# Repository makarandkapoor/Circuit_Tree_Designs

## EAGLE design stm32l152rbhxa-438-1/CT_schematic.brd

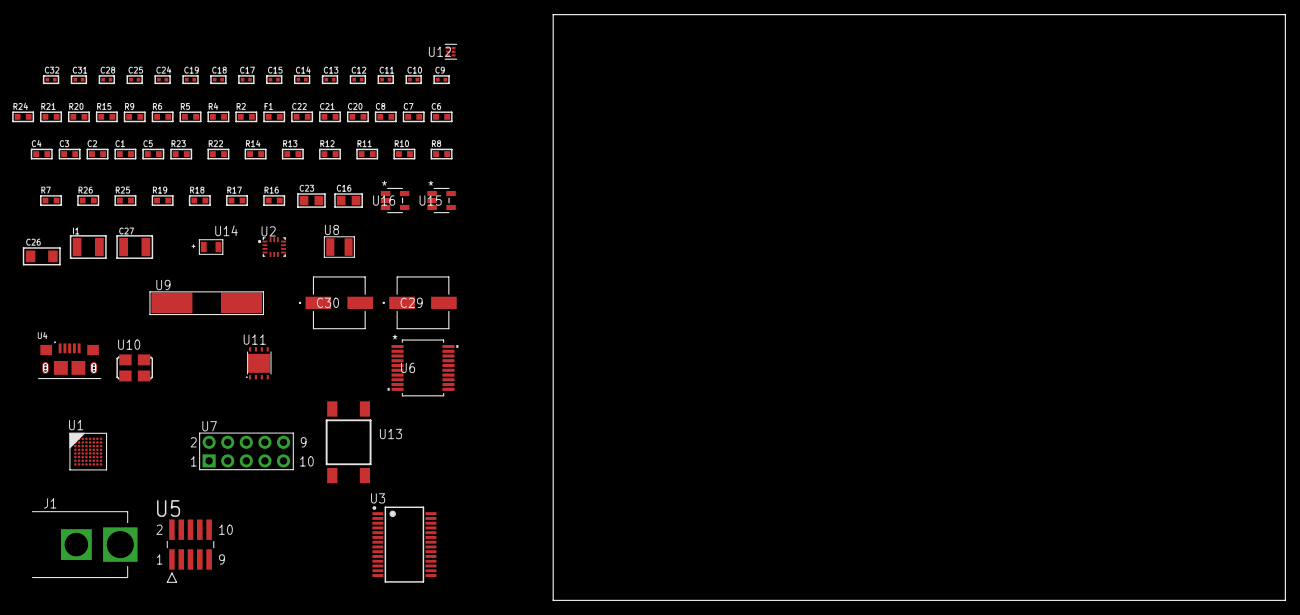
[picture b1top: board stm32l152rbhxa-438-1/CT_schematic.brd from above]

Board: 2 copper layers, 169.6 x 80.0 mm, 75 parts (0 on the bottom side), 55 nets, no tracks yet.

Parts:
C1, C2, C3, C4, C6: 1e-07; C0603
C5: 4.7e-06; C0603
C7: 1e-08; C0603
C8, C20, C21, C22: 1e-06; C0603
C9, C10, C11, C12: 1e-11; C0402
C13, C14, C15, C17, C18, C19, C28: 1e-07; C0402
C16, C23: 4.7e-06; C0805
C24, C25, C31, C32: 1e-08; C0402
C26: 1e-05; C1206
C27: 1e-05; C1210
C29, C30: 0.0001; EXV-9H
F1: 240.0; L0603
I1: 1.5e-05; L1210
J1: PJ-037B; PJ-037B_PACKAGE
R2, R21: 1000.0; R0603
R4, R9: 4700.0; R0603
R5, R6: 2200.0; R0603
R7, R8, R10, R11, R12, R13, R14, R22, R23: 10000.0; R0603
R15: 5.0; R0603
R16, R17, R18, R19: 100000.0; R0603
R20: 2231.0; R0603
R24: 9100.0; R0603
R25: 680000.0; R0603
R26: 120000.0; R0603
U1: STM32L152RBH6A; TFBGA64
U2: BMG250; LGA-14
U3: FT232RL-REEL; SSOP-28
U4: 10118193-0001LF; FCI_10118193-0001LF
U5: FTSH-105-01-L-DV-K; SAMTEC_FTSH-105-01-L-DV-K
U6: MAX3218EAP+T; SSOP-20
U7: HTSS-105-01-G-D
U8: ABS07-32.768KHZ-7-T
U9: ABLS-25.000MHZ-B2F-T
U10: ASFL1-12MHZ-NCS; ASFL1
U11: LP3878SDX-ADJ/NOPB; WSON-8
U12: TPS3895ADRYR; SON-6
U13: 4-1437565-2; SW_4-1437565-2
U14: Q65110A2395; LGM67K-G1J2-24-Z
U15, U16: nc7sz125m5x; NC7SZ125M5X

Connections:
CLK_CRYSTAL_U1_A1: C9.1, U1.A1, U8.1
CLK_CRYSTAL_U1_B1: C10.1, U1.B1, U8.2
CLK_CRYSTAL_U1_C1: C11.1, U1.C1, U9.1
CLK_CRYSTAL_U1_D1: C12.1, U1.D1, U9.2
CLK_U3_27: U3.27, U10.3
GND: C1.2, C2.2, C3.2, C4.2, C5.2, C6.2, C7.2, C8.2, C9.2, C10.2, C11.2, C12.2, C13.2, C14.2, C15.2, C16.2, C17.2, C18.2, C19.2, C20.2, C21.2, C22.2, C24.2, C25.2, C26.2, C27.2, C28.2, C29.2, C30.2, C31.2, C32.2, J1.2, R2.2, R7.2, R11.2, R15.2, R21.2, R24.2, R26.2, U1.C2, U1.D4, U1.D5, U1.D6, U1.F1, U2.1, U2.6, U2.7, U3.7, U3.18, U3.21, U3.25, U3.26, U4.5, U4.6, U4.7, U4.8, U4.9, U5.3, U5.5, U6.5, U6.17, U6.20, U7.9, U10.2, U11.3, U11.PAD, U12.2, U14.C, U15.2, U15.3, U16.1, U16.3
NET_U1_A3: R6.1, U1.A3, U2.14
NET_U1_B2: C6.1, U1.B2
NET_U1_B3: R5.1, U1.B3, U2.13
NET_U1_B4: R7.1, U1.B4
NET_U1_E1: R4.1, U1.E1, U16.4
NET_U1_H1: C7.1, C8.1, F1.1, U1.G1, U1.H1
NET_U1_H8: U13.3, U13.4
NET_U2_12: R8.1, U2.12
NET_U3_14: R10.1, U3.14
NET_U3_17: C17.1, U3.17
NET_U3_19: R11.1, U3.19
NET_U4_1: R9.1, U4.1
NET_U4_2: U3.16, U4.2
NET_U4_3: U3.15, U4.3
NET_U5_9: R15.1, U5.9
NET_U6_1: I1.1, U6.1
NET_U6_2: R16.1, U6.2
NET_U6_3: R17.1, U6.3
NET_U6_4: R18.1, U6.4
NET_U6_15: C22.1, U6.15
NET_U6_16: C23.2, U6.16
NET_U6_18: C23.1, U6.18
NET_U6_19: C21.1, U6.19
NET_U7_3: U6.12, U7.3
NET_U7_4: U6.11, U7.4
NET_U7_5: U6.14, U7.5
NET_U7_6: U6.13, U7.6
NET_U11_1: C25.1, U11.1
NET_U11_6: R20.2, R21.1, U11.6
NET_U11_8: R19.1, U11.8
NET_U12_1: R23.1, R24.1, U12.1
NET_U12_3: R25.2, R26.1, U12.3
NET_U12_4: R22.1, U12.4, U15.4, U16.2
NET_U13_1: R2.1, U13.1, U13.2
PROC_GPIO_TO_U2_INT1: U1.A2, U2.4
PROC_SYS_JTCK_SWCLK: R13.1, U1.A7, U5.4
PROC_SYS_JTDO_TRACESWO: U1.A5, U5.6
PROC_SYS_JTMS_SWDIO: R14.1, U1.A8, U5.2
PROC_USART1_CTS: U1.C8, U3.3
PROC_USART1_RTS: U1.B8, U3.11
PROC_USART1_RX: U1.C3, U3.1
PROC_USART1_TX: U1.C7, U3.5
PROC_USART2_CTS: U1.G2, U6.8
PROC_USART2_RTS: U1.H2, U6.10
PROC_USART2_RX: U1.G3, U6.9
PROC_USART2_TX: U1.F3, U6.7
RST_OUT_U5_JTAG_RST_B: R12.1, U5.10, U15.1
VCC_S1_9V3: C26.1, C29.1, C30.1, J1.1, R19.2, U11.4
VCC_TIER1_3V3: C1.1, C2.1, C3.1, C4.1, C5.1, C13.1, C14.1, C15.1, C16.1, C18.1, C19.1, C20.1, C24.1, C27.1, C28.1, C31.1, C32.1, F1.2, I1.2, R4.2, R5.2, R6.2, R8.2, R10.2, R12.2, R13.2, R14.2, R16.2, R17.2, R18.2, R20.1, R22.2, R23.2, R25.1, U1.D2, U1.E4, U1.E5, U1.E6, U2.5, U2.8, U3.4, U3.20, U5.1, U6.6, U10.4, U11.5, U12.6, U15.5, U16.5

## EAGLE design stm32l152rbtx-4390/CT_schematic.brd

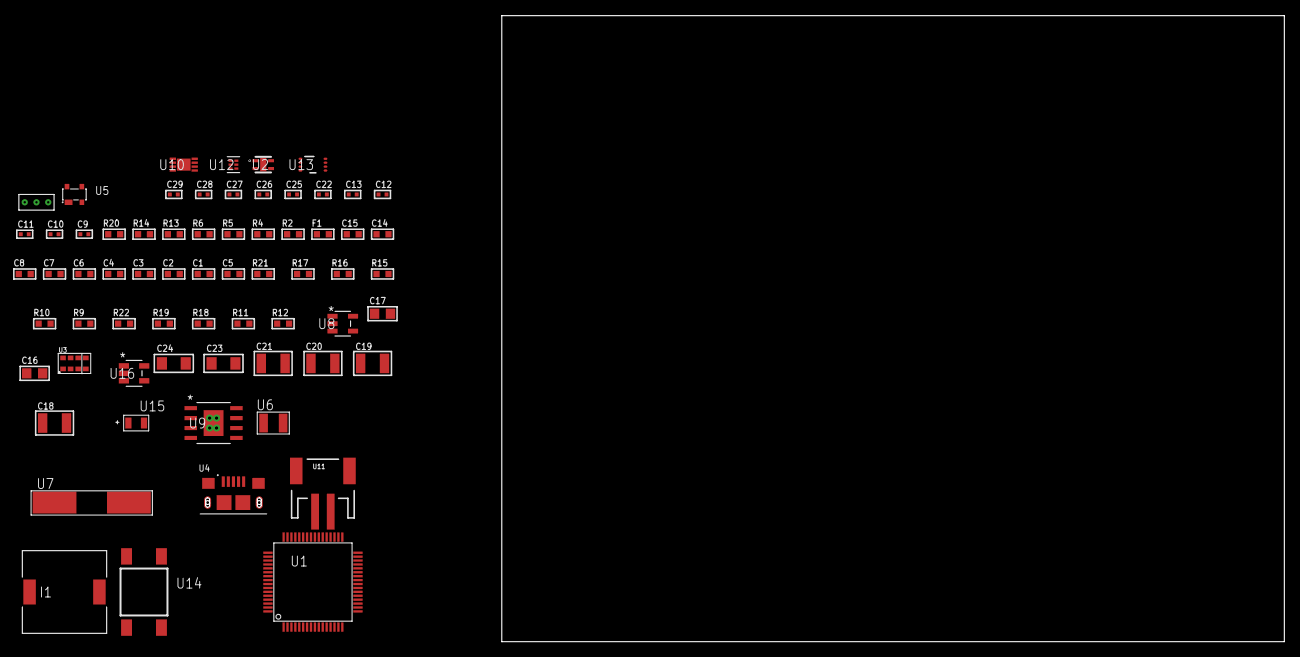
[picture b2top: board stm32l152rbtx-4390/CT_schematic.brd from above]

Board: 2 copper layers, 66 parts (0 on the bottom side), 34 nets, no tracks yet.

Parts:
C1, C2, C3, C4, C6: 1e-07; C0603
C5: 4.7e-06; C0603
C7: 1e-08; C0603
C8, C14, C15: 1e-06; C0603
C9, C10, C11, C12: 1e-11; C0402
C13, C22, C26, C28: 1e-07; C0402
C16, C17: 1e-05; C0805
C18, C19, C20, C21: 1e-05; C1210
C23, C24: 1e-05; C1206
C25, C27, C29: 1e-08; C0402
F1: 240.0; L0603
I1: 5.2e-06; DR1040
R2: 1000.0; R0603
R4: 4700.0; R0603
R5, R6, R14: 2200.0; R0603
R9, R10, R15, R16, R21: 10000.0; R0603
R11: 490000.0; R0603
R12: 1000000.0; R0603
R13: 3600.0; R0603
R17: 82000.0; R0603
R18: 300000.0; R0603
R19: 120000.0; R0603
R20: 2000.0; R0603
R22: 200000.0; R0603
U1: STM32L152RBT6; LQFP64
U2: Si7034-A10-IM; SI7034-A10-IM
U3: TMD27711; SMD-8
U4: 10118193-0001LF; FCI_10118193-0001LF
U5: prtr5v0u2ax; SOT143B
U6: ABS07-32.768KHZ-7-T
U7: ABLS-25.000MHZ-B2F-T
U8: ltc3406es5; TSOT-23-5
U9: MIC5234YME; SOIC-8_EP
U10: MCP73831T-2ACI/MC; DFN8_2X3MC
U11: S2B-PH-SM4-TB(LF)(SN); JST-2-SMD
U12: TPS3895ADRYR; SON-6
U13: LSF0102DCTR; DCU0008A_N
U14: 4-1437565-2; SW_4-1437565-2
U15: Q65110A2395; LGM67K-G1J2-24-Z
U16: nc7sz125m5x; NC7SZ125M5X
U17: Dummy; DUMMY_PACKAGE_139

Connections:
CLK_CRYSTAL_U1_3: C9.1, U1.3, U6.1
CLK_CRYSTAL_U1_4: C10.1, U1.4, U6.2
CLK_CRYSTAL_U1_5: C11.1, U1.5, U7.1
CLK_CRYSTAL_U1_6: C12.1, U1.6, U7.2
GND: C1.2, C2.2, C3.2, C4.2, C5.2, C6.2, C7.2, C8.2, C9.2, C10.2, C11.2, C12.2, C13.2, C14.2, C15.2, C16.2, C17.1, C17.2, C18.2, C19.2, C20.2, C21.2, C22.2, C23.2, C24.2, C25.2, C26.2, C27.2, C28.2, C29.2, R2.2, R9.2, R11.2, R14.2, R17.2, R19.2, R20.2, U1.12, U1.18, U1.31, U1.47, U1.63, U2.5, U3.3, U4.5, U4.6, U4.7, U4.8, U4.9, U5.1, U8.2, U9.7, U9.EPAD, U10.6, U10.9, U11.2, U12.2, U13.1, U15.C, U16.1, U16.3, U17.1
INPUT_USBPOWER_5V: C23.1, R21.2, U4.1, U5.4, U10.1, U10.2
NET_U1_1: C6.1, U1.1
NET_U1_7: R4.1, U1.7, U16.4
NET_U1_13: C7.1, C8.1, F1.1, U1.13
NET_U1_58: R5.1, U1.58, U2.2
NET_U1_59: R6.1, U1.59, U2.4
NET_U1_60: R9.1, U1.60
NET_U1_62: U14.3, U14.4
NET_U3_7: R10.1, U3.7
NET_U8_3: I1.1, U8.3
NET_U8_5: R11.1, R12.1, U8.5
NET_U8_ATNET_3: I1.2, R12.2
NET_U9_4: R13.2, R14.1, U9.4
NET_U10_5: R21.1, U10.5
NET_U10_8: R20.1, U10.8
NET_U12_1: R16.1, R17.1, U12.1
NET_U12_3: R18.2, R19.1, U12.3
NET_U12_4: R15.1, U12.4, U16.2
NET_U13_8: R22.1, U13.8
NET_U14_1: R2.1, U14.1, U14.2
PROC_I2C2_SCL_TOXCVR: U3.2, U13.5
PROC_I2C2_SDA_TOXCVR: U3.8, U13.6
PROC_PC0: U1.8, U17.3
PROC_PC13_WKUP2: U1.2, U17.2
PROC_USB_DM: U1.44, U4.2, U5.3
PROC_USB_DP: U1.45, U4.3, U5.2
VCC_S1_3V7: C16.1, C18.1, C19.1, C24.1, U8.4, U9.5, U9.8, U10.3, U10.4, U11.1
VCC_TIER1_1V8: C1.1, C2.1, C3.1, C4.1, C5.1, C13.1, C17.2, C22.1, C27.1, C28.1, C29.1, F1.2, I1.2, R4.2, R5.2, R6.2, R12.2, R15.2, R16.2, R18.1, U1.19, U1.32, U1.48, U1.64, U2.1, U12.6, U13.2, U16.5
VCC_TIER1_3V0: C14.1, C15.1, C20.1, C21.1, C25.1, C26.1, R10.2, R13.1, R22.2, U3.1, U3.4, U9.1, U13.7

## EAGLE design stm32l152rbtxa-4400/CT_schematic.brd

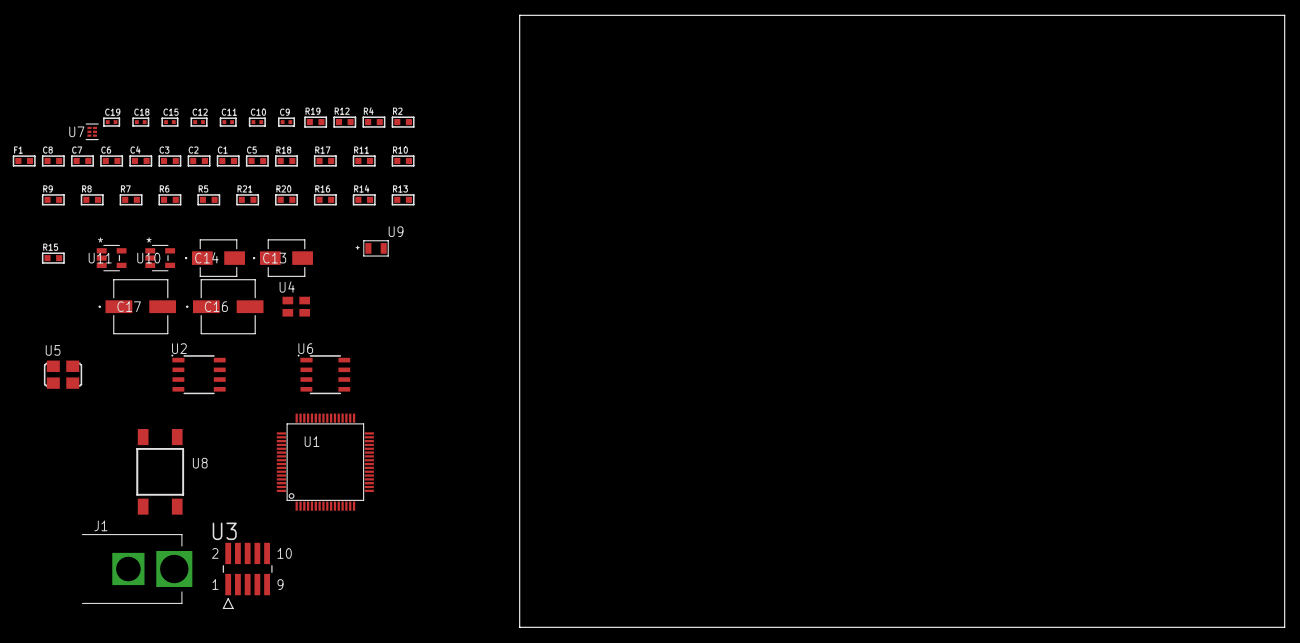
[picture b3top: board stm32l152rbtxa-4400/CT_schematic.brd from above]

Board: 2 copper layers, 100.0 x 80.0 mm, 51 parts (0 on the bottom side), 28 nets, no tracks yet.

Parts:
C1, C2, C3, C4, C6: 1e-07; C0603
C5: 4.7e-06; C0603
C7: 1e-08; C0603
C8: 1e-06; C0603
C9, C11, C12, C18, C19: 1e-08; C0402
C10, C15: 1e-07; C0402
C13: 1e-06; EXV-9B
C14: 2.2e-06; EXV-9B
C16, C17: 0.0001; EXV-9H
F1: 240.0; L0603
J1: PJ-037B; PJ-037B_PACKAGE
R2: 1000.0; R0603
R4: 4700.0; R0603
R5, R6, R7, R8, R9, R10, R11, R17, R18: 10000.0; R0603
R12: 5.0; R0603
R13, R14, R16: 100000.0; R0603
R15: 164658.62; R0603
R19: 9100.0; R0603
R20: 680000.0; R0603
R21: 120000.0; R0603
U1: STM32L152RBT6A; LQFP64
U2: AT25640B-SSHL-T; SOIC-8
U3: FTSH-105-01-L-DV-K; SAMTEC_FTSH-105-01-L-DV-K
U4: ASEK-32.768KHz-ECST; ASEK
U5: ASFL1-25MHZ-NCS; ASFL1
U6: LP2954AIMX/NOPB; LP2954
U7: TPS3895ADRYR; SON-6
U8: 4-1437565-2; SW_4-1437565-2
U9: Q65110A2395; LGM67K-G1J2-24-Z
U10, U11: nc7sz125m5x; NC7SZ125M5X

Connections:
CLK_U1_3: U1.3, U4.3
CLK_U1_5: U1.5, U5.3
GND: C1.2, C2.2, C3.2, C4.2, C5.2, C6.2, C7.2, C8.2, C9.2, C10.2, C11.2, C12.2, C13.2, C14.2, C15.2, C16.2, C17.2, C18.2, C19.2, J1.2, R2.2, R5.2, R12.2, R16.2, R19.2, R21.2, U1.12, U1.18, U1.31, U1.47, U1.63, U2.4, U3.3, U3.5, U4.2, U5.2, U6.4, U7.2, U9.C, U10.2, U10.3, U11.1, U11.3
NET_U1_1: C6.1, U1.1
NET_U1_7: R4.1, U1.7, U11.4
NET_U1_13: C7.1, C8.1, F1.1, U1.13
NET_U1_60: R5.1, U1.60
NET_U1_62: U8.3, U8.4
NET_U2_3: R6.1, U2.3
NET_U2_7: R8.1, U2.7
NET_U3_9: R12.1, U3.9
NET_U6_3: R14.1, U6.3
NET_U6_5: R13.1, U6.5
NET_U6_7: R15.2, R16.1, U6.7
NET_U7_1: R18.1, R19.1, U7.1
NET_U7_3: R20.2, R21.1, U7.3
NET_U7_4: R17.1, U7.4, U10.4, U11.2
NET_U8_1: R2.1, U8.1, U8.2
PROC_SPI1_MISO: U1.22, U2.2
PROC_SPI1_MOSI: U1.23, U2.5
PROC_SPI1_NSS: R7.1, U1.20, U2.1
PROC_SPI1_SCK: U1.21, U2.6
PROC_SYS_JTCK_SWCLK: R10.1, U1.49, U3.4
PROC_SYS_JTDO_TRACESWO: U1.55, U3.6
PROC_SYS_JTMS_SWDIO: R11.1, U1.46, U3.2
RST_OUT_U3_JTAG_RST_B: R9.1, U3.10, U10.1
VCC_S1_12V1: C13.1, C16.1, C17.1, J1.1, R14.2, U6.8
VCC_TIER1_3V3: C1.1, C2.1, C3.1, C4.1, C5.1, C9.1, C10.1, C11.1, C12.1, C14.1, C15.1, C18.1, C19.1, F1.2, R4.2, R6.2, R7.2, R8.2, R9.2, R10.2, R11.2, R13.2, R15.1, R17.2, R18.2, R20.1, U1.19, U1.32, U1.48, U1.64, U2.8, U3.1, U4.4, U5.4, U6.1, U7.6, U10.5, U11.5

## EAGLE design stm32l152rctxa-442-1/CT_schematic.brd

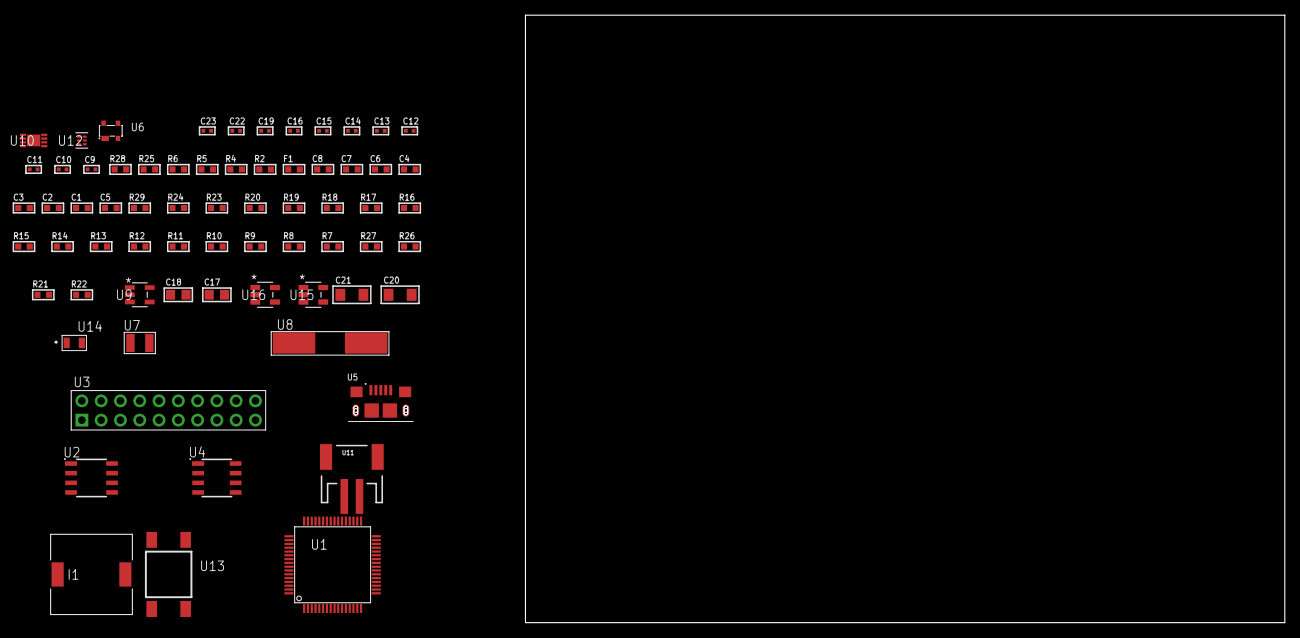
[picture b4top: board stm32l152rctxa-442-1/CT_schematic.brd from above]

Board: 2 copper layers, 122.6 x 80.0 mm, 68 parts (0 on the bottom side), 43 nets, no tracks yet.

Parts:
C1, C2, C3, C4, C6: 1e-07; C0603
C5: 4.7e-06; C0603
C7: 1e-08; C0603
C8: 1e-06; C0603
C9, C10, C11, C12: 1e-11; C0402
C13, C16, C22, C23: 1e-08; C0402
C14, C15, C19: 1e-07; C0402
C17, C18: 1e-05; C0805
C20, C21: 1e-05; C1206
F1: 240.0; L0603
I1: 3.8e-06; DR1040
R2: 1000.0; R0603
R4: 4700.0; R0603
R5, R6: 2200.0; R0603
R7, R8, R9, R10, R11, R12, R13, R14, R15, R16, R17, R18, R19, R20, R23, R24, R29: 10000.0; R0603
R21: 220000.0; R0603
R22: 1000000.0; R0603
R25: 9100.0; R0603
R26: 680000.0; R0603
R27: 120000.0; R0603
R28: 2000.0; R0603
U1: STM32L152RCT6A; LQFP64
U2: AT25M02-SSHD-T; SOIC-8
U3: TST-110-05-T-D-RA
U4: AT24C02D-SSHM-T; AT24C02D
U5: 10118193-0001LF; FCI_10118193-0001LF
U6: prtr5v0u2ax; SOT143B
U7: ABS07-32.768KHZ-7-T
U8: ABLS-25.000MHZ-B2F-T
U9: ltc3406es5; TSOT-23-5
U10: MCP73831T-2ACI/MC; DFN8_2X3MC
U11: S2B-PH-SM4-TB(LF)(SN); JST-2-SMD
U12: TPS3895ADRYR; SON-6
U13: 4-1437565-2; SW_4-1437565-2
U14: Q65110A2395; LGM67K-G1J2-24-Z
U15, U16: nc7sz125m5x; NC7SZ125M5X

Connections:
CLK_CRYSTAL_U1_3: C9.1, U1.3, U7.1
CLK_CRYSTAL_U1_4: C10.1, U1.4, U7.2
CLK_CRYSTAL_U1_5: C11.1, U1.5, U8.1
CLK_CRYSTAL_U1_6: C12.1, U1.6, U8.2
GND: C1.2, C2.2, C3.2, C4.2, C5.2, C6.2, C7.2, C8.2, C9.2, C10.2, C11.2, C12.2, C13.2, C14.2, C15.2, C16.2, C17.2, C18.1, C18.2, C19.2, C20.2, C21.2, C22.2, C23.2, R2.2, R7.2, R16.2, R17.2, R19.2, R20.2, R21.2, R25.2, R27.2, R28.2, U1.12, U1.18, U1.31, U1.47, U1.63, U2.4, U3.4, U3.6, U3.8, U3.10, U3.12, U3.14, U3.16, U3.18, U3.20, U4.4, U5.5, U5.6, U5.7, U5.8, U5.9, U6.1, U9.2, U10.6, U10.9, U11.2, U12.2, U14.C, U15.2, U15.3, U16.1, U16.3
INPUT_USBPOWER_5V: C20.1, R29.2, U5.1, U6.4, U10.1, U10.2
NET_U1_1: C6.1, U1.1
NET_U1_7: R4.1, U1.7, U16.4
NET_U1_13: C7.1, C8.1, F1.1, U1.13
NET_U1_58: R5.1, U1.58, U4.6
NET_U1_59: R6.1, U1.59, U4.5
NET_U1_60: R7.1, U1.60
NET_U1_62: U13.3, U13.4
NET_U2_3: R8.1, U2.3
NET_U2_7: R10.1, U2.7
NET_U3_19: R16.1, U3.19
NET_U4_1: R18.1, U4.1
NET_U4_2: R19.1, U4.2
NET_U4_3: R20.1, U4.3
NET_U4_7: R17.1, U4.7
NET_U9_3: I1.1, U9.3
NET_U9_5: R21.1, R22.1, U9.5
NET_U9_ATNET_3: I1.2, R22.2
NET_U10_5: R29.1, U10.5
NET_U10_8: R28.1, U10.8
NET_U12_1: R24.1, R25.1, U12.1
NET_U12_3: R26.2, R27.1, U12.3
NET_U12_4: R23.1, U12.4, U15.4, U16.2
NET_U13_1: R2.1, U13.1, U13.2
PROC_SPI1_MISO: U1.22, U2.2
PROC_SPI1_MOSI: U1.23, U2.5
PROC_SPI1_NSS: R9.1, U1.20, U2.1
PROC_SPI1_SCK: U1.21, U2.6
PROC_SYS_JTCK_SWCLK: R14.1, U1.49, U3.9
PROC_SYS_JTDI: R12.1, U1.50, U3.5
PROC_SYS_JTDO_TRACESWO: U1.55, U3.13
PROC_SYS_JTMS_SWDIO: R13.1, U1.46, U3.7
PROC_SYS_JTRST: R11.1, U1.56, U3.3
PROC_USB_DM: U1.44, U5.2, U6.3
PROC_USB_DP: U1.45, U5.3, U6.2
RST_OUT_U3_SRESET_B: R15.1, U3.15, U15.1
VCC_S1_3V7: C17.1, C21.1, U9.4, U10.3, U10.4, U11.1
VCC_TIER1_3V3: C1.1, C2.1, C3.1, C4.1, C5.1, C13.1, C14.1, C15.1, C16.1, C18.2, C19.1, C22.1, C23.1, F1.2, I1.2, R4.2, R5.2, R6.2, R8.2, R9.2, R10.2, R11.2, R12.2, R13.2, R14.2, R15.2, R18.2, R22.2, R23.2, R24.2, R26.1, U1.19, U1.32, U1.48, U1.64, U2.8, U3.1, U3.2, U4.8, U12.6, U15.5, U16.5

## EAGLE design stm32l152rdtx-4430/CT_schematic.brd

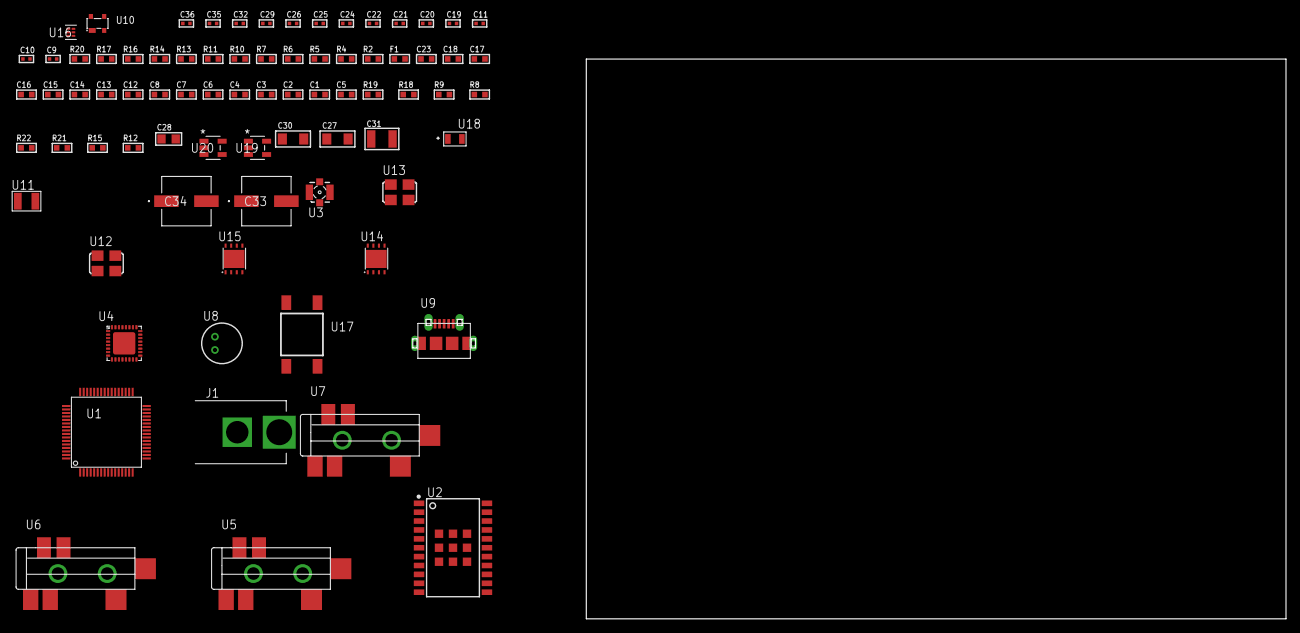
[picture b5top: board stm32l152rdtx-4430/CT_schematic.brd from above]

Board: 2 copper layers, 124.8 x 80.0 mm, 78 parts (0 on the bottom side), 49 nets, no tracks yet.

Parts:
C1, C2, C3, C4, C6: 1e-07; C0603
C5: 4.7e-06; C0603
C7: 1e-08; C0603
C8, C12, C13, C14, C15, C16, C17, C18, C23: 1e-06; C0603
C9, C10: 1e-11; C0402
C11, C19, C20, C21, C22, C32: 1e-07; C0402
C24, C25, C26, C29, C35, C36: 1e-08; C0402
C27, C30: 1e-05; C1206
C28: 1e-05; C0805
C31: 1e-05; C1210
C33, C34: 0.0001; EXV-9H
F1: 240.0; L0603
J1: PJ-037B; PJ-037B_PACKAGE
R2, R14, R17: 1000.0; R0603
R4, R5: 4700.0; R0603
R6, R7: 2200.0; R0603
R8, R9, R18, R19: 10000.0; R0603
R10, R11: 1270.0; R0603
R12, R15: 100000.0; R0603
R13: 200.0; R0603
R16: 2231.0; R0603
R20: 9100.0; R0603
R21: 680000.0; R0603
R22: 120000.0; R0603
U1: STM32L152RDT6; LQFP64
U2: A2200-A
U3: 73412-0114; COAXIAL_C
U4: SGTL5000XNAA3; QFN-32
U5, U6, U7: SJ-43515TS-SMT-TR
U8: WM-64PCT; WM-64PC
U9: 47590-0001; MICRO_USB_AB
U10: prtr5v0u2ax; SOT143B
U11: ABS07-32.768KHZ-7-T
U12: ASFL-24.57MHZ-NCS; ASFL1
U13: ASFL1-25MHZ-NCS; ASFL1
U14, U15: LP3878SDX-ADJ/NOPB; WSON-8
U16: TPS3895ADRYR; SON-6
U17: 4-1437565-2; SW_4-1437565-2
U18: Q65110A2395; LGM67K-G1J2-24-Z
U19, U20: nc7sz125m5x; NC7SZ125M5X

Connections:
CLK_CRYSTAL_U1_3: C9.1, U1.3, U11.1
CLK_CRYSTAL_U1_4: C10.1, U1.4, U11.2
CLK_U1_5: U1.5, U13.3
CLK_U4_21: U4.21, U12.3
GND: C1.2, C2.2, C3.2, C4.2, C5.2, C6.2, C7.2, C8.2, C9.2, C10.2, C11.2, C19.2, C20.2, C21.2, C22.2, C23.2, C24.2, C25.2, C26.2, C27.2, C28.2, C29.2, C30.2, C31.2, C32.2, C33.2, C34.2, C35.2, C36.2, J1.2, R2.2, R8.2, R11.2, R14.2, R17.2, R20.2, R22.2, U1.12, U1.18, U1.31, U1.47, U1.63, U2.7, U2.8, U2.23, U2.24, U2.25, U2.26, U2.27, U2.28, U2.29, U2.30, U2.31, U4.1, U4.3, U4.7, U4.EXP, U6.1, U7.1, U8.2, U9.5, U9.6, U9.7, U9.8, U9.9, U10.1, U12.2, U13.2, U14.3, U14.PAD, U15.3, U15.PAD, U16.2, U18.C, U19.1, U19.3, U20.1, U20.3
NET_U1_1: C6.1, U1.1
NET_U1_7: R5.1, U1.7, U20.4
NET_U1_13: C7.1, C8.1, F1.1, U1.13
NET_U1_58: R6.1, U1.58, U2.15
NET_U1_59: R7.1, U1.59, U2.16
NET_U1_60: R8.1, U1.60
NET_U1_62: U17.3, U17.4
NET_U2_2: R9.2, U2.2
NET_U2_17: R9.1, U2.17
NET_U2_22: R4.1, U2.22, U19.4
NET_U3_1: U2.11, U3.1
NET_U3_2: U2.10, U3.2, U3.3, U3.4
NET_U4_10: C22.1, U4.10
NET_U4_29: R10.1, U4.29
NET_U4_31: R11.1, U4.31
NET_U5_1: U4.4, U5.1
NET_U5_2: U4.2, U5.2
NET_U5_5: U4.6, U5.5
NET_U6_2: C13.1, U6.2
NET_U6_5: C12.1, U6.5
NET_U7_2: C15.1, C16.1, U7.2
NET_U7_5: C14.1, U7.5
NET_U7_13: C15.2, C16.2
NET_U8_1: C17.1, C18.1, C23.1, U4.16, U8.1
NET_U8_15: C17.2, C18.2
NET_U10_4: U9.1, U10.4
NET_U14_1: C26.1, U14.1
NET_U14_6: R13.2, R14.1, U14.6
NET_U14_8: R12.1, U14.8
NET_U15_1: C29.1, U15.1
NET_U15_6: R16.2, R17.1, U15.6
NET_U15_8: R15.1, U15.8
NET_U16_1: R19.1, R20.1, U16.1
NET_U16_3: R21.2, R22.1, U16.3
NET_U16_4: R18.1, U16.4, U19.2, U20.2
NET_U17_1: R2.1, U17.1, U17.2
PROC_I2S2_CK: U1.34, U4.24
PROC_I2S2_SD: U1.36, U4.26
PROC_I2S2_WS: U1.33, U4.23
PROC_USB_DM: U1.44, U9.2, U10.3
PROC_USB_DP: U1.45, U9.3, U10.2
VCC_S1_8V6: C27.1, C30.1, C33.1, C34.1, J1.1, R12.2, R15.2, U14.4, U15.4
VCC_TIER1_1V2: C19.1, C28.1, R13.1, U4.30, U14.5
VCC_TIER1_3V3: C1.1, C2.1, C3.1, C4.1, C5.1, C11.1, C20.1, C21.1, C24.1, C25.1, C31.1, C32.1, C35.1, C36.1, F1.2, R4.2, R5.2, R6.2, R7.2, R10.2, R16.1, R18.2, R19.2, R21.1, U1.19, U1.32, U1.48, U1.64, U2.20, U4.5, U4.20, U12.4, U13.4, U15.5, U16.6, U19.5, U20.5

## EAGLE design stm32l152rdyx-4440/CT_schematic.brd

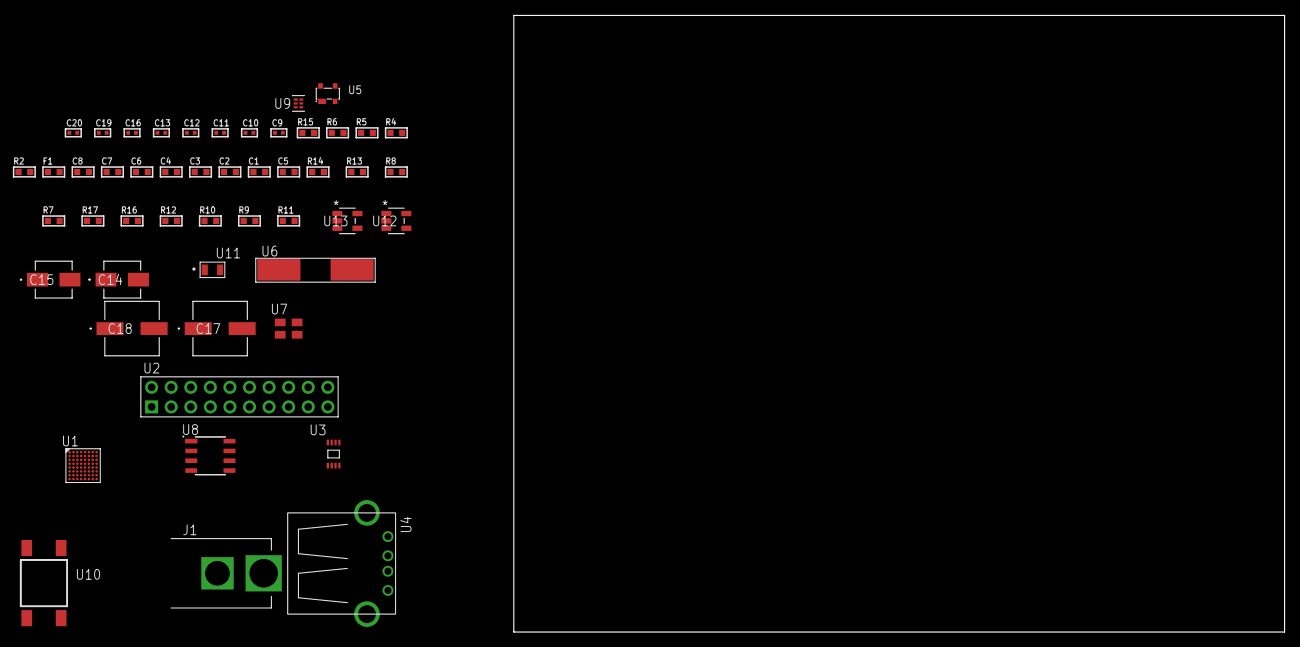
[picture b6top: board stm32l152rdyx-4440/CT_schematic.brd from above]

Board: 2 copper layers, 100.0 x 80.0 mm, 50 parts (0 on the bottom side), 27 nets, no tracks yet.

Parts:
C1, C2, C3, C4, C6: 1e-07; C0603
C5: 4.7e-06; C0603
C7: 1e-08; C0603
C8: 1e-06; C0603
C9, C10: 1e-11; C0402
C11, C16: 1e-07; C0402
C12, C13, C19, C20: 1e-08; C0402
C14: 1e-06; EXV-9B
C15: 2.2e-06; EXV-9B
C17, C18: 0.0001; EXV-9H
F1: 240.0; L0603
J1: PJ-037B; PJ-037B_PACKAGE
R2: 1000.0; R0603
R4: 4700.0; R0603
R5, R6: 2200.0; R0603
R7, R8, R13, R14: 10000.0; R0603
R9, R10, R12: 100000.0; R0603
R11: 164658.62; R0603
R15: 9100.0; R0603
R16: 680000.0; R0603
R17: 120000.0; R0603
U1: STM32L152RDY6; WLCSP64
U2: TST-110-05-T-D-RA
U3: 24AA00T-I/MNY; TDFN-8/6MM
U4: 61400416021; USB-A-H
U5: prtr5v0u2ax; SOT143B
U6: ABLS-25.000MHZ-B2F-T
U7: ASEK-32.768KHz-ECST; ASEK
U8: LP2954AIMX/NOPB; LP2954
U9: TPS3895ADRYR; SON-6
U10: 4-1437565-2; SW_4-1437565-2
U11: Q65110A2395; LGM67K-G1J2-24-Z
U12, U13: nc7sz125m5x; NC7SZ125M5X

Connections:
CLK_CRYSTAL_U1_D7: C9.1, U1.D7, U6.1
CLK_CRYSTAL_U1_D8: C10.1, U1.D8, U6.2
CLK_U1_B8: U1.B8, U7.3
GND: C1.2, C2.2, C3.2, C4.2, C5.2, C6.2, C7.2, C8.2, C9.2, C10.2, C11.2, C12.2, C13.2, C14.2, C15.2, C16.2, C17.2, C18.2, C19.2, C20.2, J1.2, R2.2, R7.2, R12.2, R15.2, R17.2, U1.A7, U1.B1, U1.E7, U1.F5, U1.H2, U2.4, U2.6, U2.8, U2.10, U2.12, U2.14, U2.16, U2.18, U2.20, U3.4, U4.4, U4.5, U4.6, U5.1, U7.2, U8.4, U9.2, U11.C, U12.2, U12.3, U13.1, U13.3
NET_U1_A6: R7.1, U1.A6
NET_U1_B5: R5.1, U1.B5, U3.6
NET_U1_B6: R6.1, U1.B6, U3.5
NET_U1_C6: C6.1, U1.C6
NET_U1_C7: R4.1, U1.C7, U13.4
NET_U1_G8: C7.1, C8.1, F1.1, U1.G8
NET_U1_H8: U10.3, U10.4
NET_U5_4: U4.1, U5.4
NET_U8_3: R10.1, U8.3
NET_U8_5: R9.1, U8.5
NET_U8_7: R11.2, R12.1, U8.7
NET_U9_1: R14.1, R15.1, U9.1
NET_U9_3: R16.2, R17.1, U9.3
NET_U9_4: R13.1, U9.4, U12.4, U13.2
NET_U10_1: R2.1, U10.1, U10.2
PROC_SYS_JTCK_SWCLK: U1.B2, U2.9
PROC_SYS_JTDO_TRACESWO: U1.A4, U2.13
PROC_SYS_JTMS_SWDIO: U1.D4, U2.7
PROC_USB_DM: U1.C1, U4.2, U5.3
PROC_USB_DP: U1.C2, U4.3, U5.2
RST_OUT_U2_SRESET_B: R8.1, U2.15, U12.1
VCC_S1_8V3: C14.1, C17.1, C18.1, J1.1, R10.2, U8.8
VCC_TIER1_3V3: C1.1, C2.1, C3.1, C4.1, C5.1, C11.1, C12.1, C13.1, C15.1, C16.1, C19.1, C20.1, F1.2, R4.2, R5.2, R6.2, R8.2, R9.2, R11.1, R13.2, R14.2, R16.1, U1.A1, U1.A8, U1.G6, U1.H1, U2.1, U3.8, U7.4, U8.1, U9.6, U12.5, U13.5

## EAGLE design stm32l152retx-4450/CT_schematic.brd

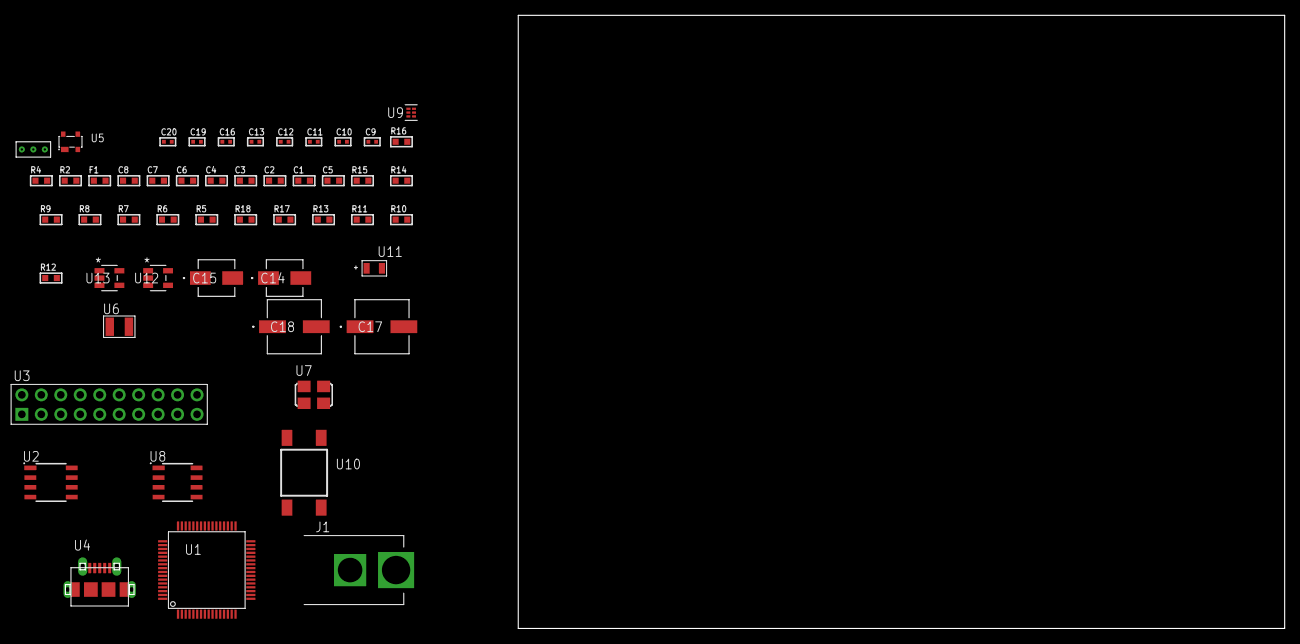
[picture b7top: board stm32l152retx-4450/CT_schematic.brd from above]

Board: 2 copper layers, 159.1 x 80.0 mm, 52 parts (0 on the bottom side), 33 nets, no tracks yet.

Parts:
C1, C2, C3, C4, C6: 1e-07; C0603
C5: 4.7e-06; C0603
C7: 1e-08; C0603
C8: 1e-06; C0603
C9, C10: 1e-11; C0402
C11, C13, C19, C20: 1e-08; C0402
C12, C16: 1e-07; C0402
C14: 1e-06; EXV-9B
C15: 2.2e-06; EXV-9B
C17, C18: 0.0001; EXV-9H
F1: 240.0; L0603
J1: PJ-037B; PJ-037B_PACKAGE
R2: 1000.0; R0603
R4: 4700.0; R0603
R5, R6, R7, R8, R9, R14, R15: 10000.0; R0603
R10, R11, R13: 100000.0; R0603
R12: 164658.62; R0603
R16: 9100.0; R0603
R17: 680000.0; R0603
R18: 120000.0; R0603
U1: STM32L152RET6; LQFP64
U2: AT25020B-SSHL-T; SOIC-8
U3: TST-110-05-T-D-RA
U4: 47590-0001; MICRO_USB_AB
U5: prtr5v0u2ax; SOT143B
U6: ABS07-32.768KHZ-7-T
U7: ASFL1-25MHZ-NCS; ASFL1
U8: LP2954AIMX/NOPB; LP2954
U9: TPS3895ADRYR; SON-6
U10: 4-1437565-2; SW_4-1437565-2
U11: Q65110A2395; LGM67K-G1J2-24-Z
U12, U13: nc7sz125m5x; NC7SZ125M5X
U14: Dummy; DUMMY_PACKAGE_112

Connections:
CLK_CRYSTAL_U1_3: C9.1, U1.3, U6.1
CLK_CRYSTAL_U1_4: C10.1, U1.4, U6.2
CLK_U1_5: U1.5, U7.3
GND: C1.2, C2.2, C3.2, C4.2, C5.2, C6.2, C7.2, C8.2, C9.2, C10.2, C11.2, C12.2, C13.2, C14.2, C15.2, C16.2, C17.2, C18.2, C19.2, C20.2, J1.2, R2.2, R5.2, R13.2, R16.2, R18.2, U1.12, U1.18, U1.31, U1.47, U1.63, U2.4, U3.4, U3.6, U3.8, U3.10, U3.12, U3.14, U3.16, U3.18, U3.20, U4.5, U4.6, U4.7, U4.8, U4.9, U5.1, U7.2, U8.4, U9.2, U11.C, U12.2, U12.3, U13.1, U13.3, U14.1
NET_U1_1: C6.1, U1.1
NET_U1_7: R4.1, U1.7, U13.4
NET_U1_13: C7.1, C8.1, F1.1, U1.13
NET_U1_60: R5.1, U1.60
NET_U1_62: U10.3, U10.4
NET_U2_3: R6.1, U2.3
NET_U2_7: R8.1, U2.7
NET_U5_4: U4.1, U5.4
NET_U8_3: R11.1, U8.3
NET_U8_5: R10.1, U8.5
NET_U8_7: R12.2, R13.1, U8.7
NET_U9_1: R15.1, R16.1, U9.1
NET_U9_3: R17.2, R18.1, U9.3
NET_U9_4: R14.1, U9.4, U12.4, U13.2
NET_U10_1: R2.1, U10.1, U10.2
PROC_PC13_WKUP2: U1.2, U14.2
PROC_PH1_OSC_OUT: U1.6, U14.3
PROC_SPI1_MISO: U1.22, U2.2
PROC_SPI1_MOSI: U1.23, U2.5
PROC_SPI1_NSS: R7.1, U1.20, U2.1
PROC_SPI1_SCK: U1.21, U2.6
PROC_SYS_JTCK_SWCLK: U1.49, U3.9
PROC_SYS_JTDO_TRACESWO: U1.55, U3.13
PROC_SYS_JTMS_SWDIO: U1.46, U3.7
PROC_USB_DM: U1.44, U4.2, U5.3
PROC_USB_DP: U1.45, U4.3, U5.2
RST_OUT_U3_SRESET_B: R9.1, U3.15, U12.1
VCC_S1_14V1: C14.1, C17.1, C18.1, J1.1, R11.2, U8.8
VCC_TIER1_3V3: C1.1, C2.1, C3.1, C4.1, C5.1, C11.1, C12.1, C13.1, C15.1, C16.1, C19.1, C20.1, F1.2, R4.2, R6.2, R7.2, R8.2, R9.2, R10.2, R12.1, R14.2, R15.2, R17.1, U1.19, U1.32, U1.48, U1.64, U2.8, U3.1, U7.4, U8.1, U9.6, U12.5, U13.5
